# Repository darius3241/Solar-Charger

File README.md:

A solar powered phone charger

# Description 

This project was created to furfill the class requirments for Power Electionics at Walla Walla University in the Spring of 2022, taught by [Dr. Rob Frohne](https://github.com/frohro). A simple solar powered phone charger intended to charge android smart phone devices was created.  

# Specifications 

The specifications for this charger are: <br/>
• 3W Solar Panel <br/>
• Take between 9 - 12 volts <br/>
• Output current of 333 mA <br/>
• Uses a buck converter <br/>

# Design 

Our design was made using the WEBENCH design tool created by Texas Instruments 

The process was simple. To use this tool we had to specify our just a few parameters which were <br/>

Input supply type (DC) <br/>
• Vin min: 14V <br/>
• Vin max: 25V <br/>

Output <br/>
• Vout: 5V <br/>
• Iout Max: 5A <br/>

Once the parameters were entered, WEBENCH gave us a variety of designs that met are specificiation. 

# Schematic

Below is the selected design we have chosen generated from WEBENCH. It was pick becasue it was one of the only designs that used components that werem't sold out. Due to the world-wide chip shortand many designs had components that were out of stock. Fortunately, we were able to find this design.

# KIcad PCB 

Using Kicad we made a another schematic and PCB to get printed off. Below is the Kicad schematic and PCB 

# Build and Test 

# Results 

Below is a photo of a completed design 

# Experimental Test Results 

Using the power supply we got: <br/>
Output voltage: 5v <br/>
Input current: 460 mA <br/>

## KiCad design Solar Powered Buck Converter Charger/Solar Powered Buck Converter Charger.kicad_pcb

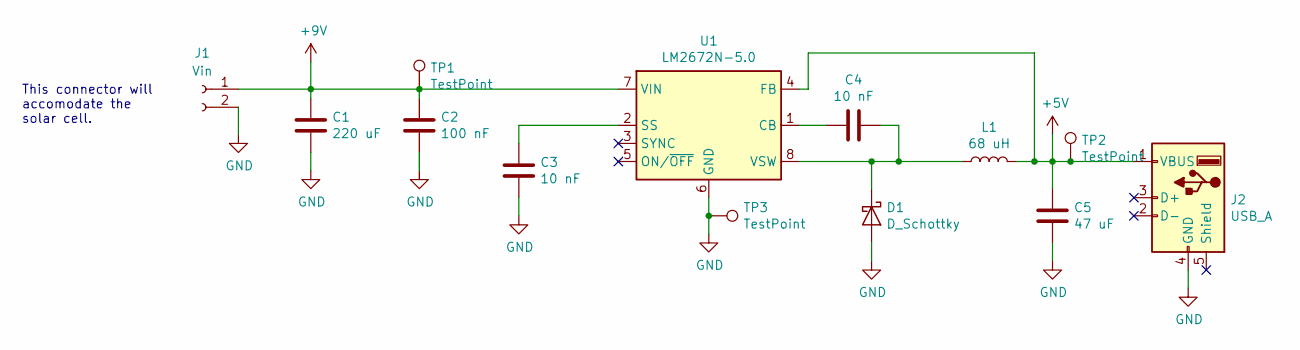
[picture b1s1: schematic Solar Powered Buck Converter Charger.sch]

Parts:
C1: 220 uF; CP_Radial_D6.3mm_P2.50mm
C2: 100 nF; C_1210
C3, C4: 10 nF; C_0805
C5: 47 uF; CP_Radial_D5.0mm_P2.00mm
D1: D_Schottky; D_Powermite_AK
J1: Vin; TerminalBlock_bornier-2_P5.08mm
J2: USB_A
L1: 68 uH; L_Wuerth_WE-PD-Typ-LS
TP1, TP2, TP3: TestPoint; Pin_Header_Straight_1x01_Pitch2.54mm
U1: LM2672N-5.0; DIP-8_W7.62mm

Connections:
+5V: C5.1, J2.1 (VBUS), L1.2, TP2.1, U1.4 (FB)
+9V: C1.1, C2.1, J1.1, TP1.1, U1.7 (VIN)
GND: C1.2, C2.2, C3.2, C5.2, D1.2 (A), J1.2, J2.4 (GND), TP3.1, U1.6 (GND)
unnamed: C3.1, U1.2 (SS)
unnamed: C4.1, D1.1 (K), L1.1, U1.8 (VSW)
unnamed: C4.2, U1.1 (CB)

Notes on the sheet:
This connector will accomodate the solar cell.

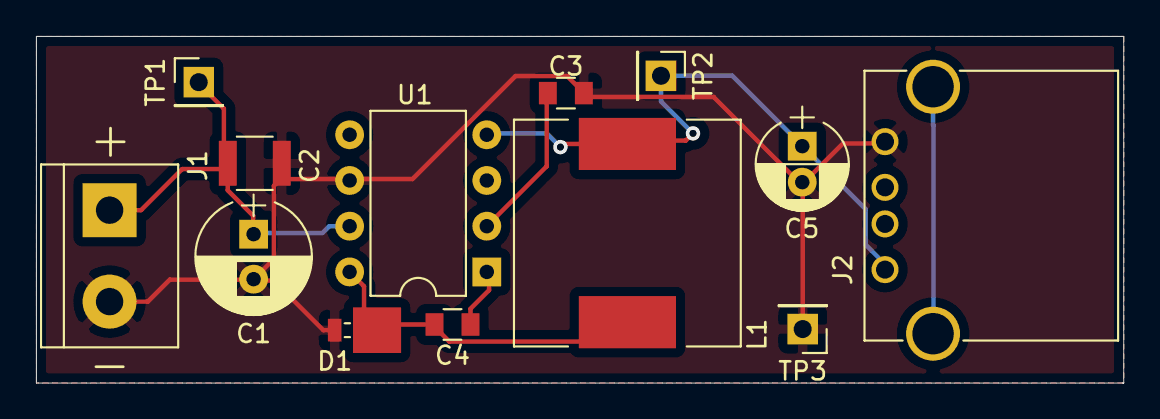
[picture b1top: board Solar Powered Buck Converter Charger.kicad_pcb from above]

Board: 2 copper layers, 60.4 x 19.3 mm, 13 parts (0 on the bottom side), 6 nets.
